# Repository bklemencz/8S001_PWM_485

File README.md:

# 8S001_PWM_485
2 or 3 Channel PWM Generator with RS485

Based on cheap 8PIN STM8S001 controller
Selectable 433Mhz EV1527/PT2262 Compatible Receiver Mode
Selectable PIR/Doppler Motion Sensor Inputs

Two versions:
One with low currect outputs, can be used as 3 channel with only RS485 active.
Other 2ch with 5A/30V NMOSFET outputs.

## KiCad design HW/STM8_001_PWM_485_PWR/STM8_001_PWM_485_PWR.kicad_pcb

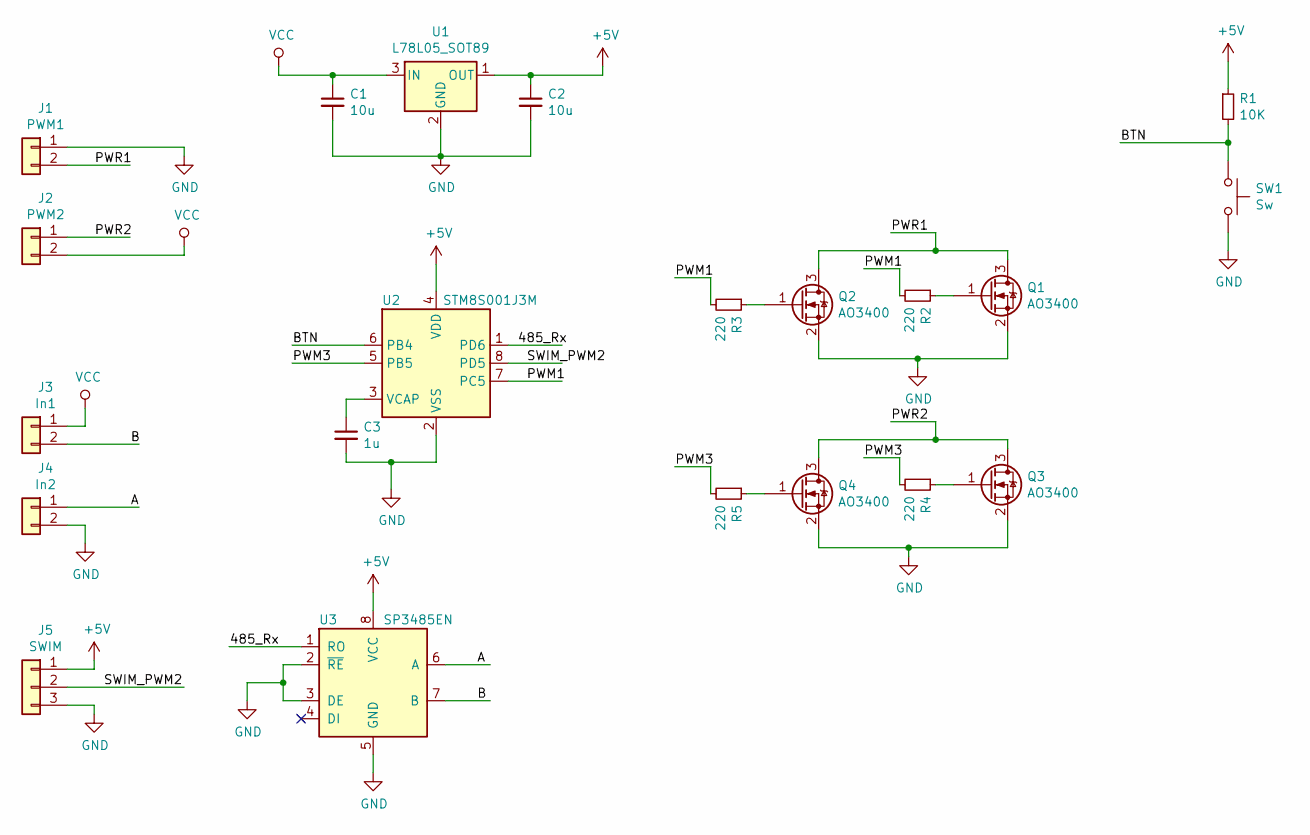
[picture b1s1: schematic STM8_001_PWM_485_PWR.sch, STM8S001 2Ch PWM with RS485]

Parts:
C1, C2: 10u; C_1206_3216Metric
C3: 1u; C_0805_2012Metric
J1: PWM1; TerminalBlock_Phoenix_PT-1,5-2-3.5-H_1x02_P3.50mm_Horizontal
J2: PWM2; TerminalBlock_Phoenix_PT-1,5-2-3.5-H_1x02_P3.50mm_Horizontal
J3: In1; TerminalBlock_Phoenix_PT-1,5-2-3.5-H_1x02_P3.50mm_Horizontal
J4: In2; TerminalBlock_Phoenix_PT-1,5-2-3.5-H_1x02_P3.50mm_Horizontal
J5: SWIM; PinHeader_1x03_P2.54mm_Vertical
Q1, Q2, Q3, Q4: AO3400; SOT-23
R1: 10K; R_0805_2012Metric
R2, R3, R4, R5: 220; R_0805_2012Metric
SW1: Sw; SW_SPST_CK_RS282G05A3
U1: L78L05_SOT89; SOT-89-3_Handsoldering
U2: STM8S001J3M; SOIC-8_3.9x4.9mm_P1.27mm
U3: SP3485EN; SOIC-8_3.9x4.9mm_P1.27mm

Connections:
+5V: C2.1, J5.1, R1.1, U1.1 (OUT), U2.4 (VDD), U3.8 (VCC)
/485_Rx: U2.1 (PD6), U3.1 (RO)
/A: J4.1, U3.6 (A)
/B: J3.2, U3.7 (B)
/BTN: R1.2, SW1.1, U2.6 (PB4)
/PWM1: R2.2, R3.2, U2.7 (PC5)
/PWM3: R4.2, R5.2, U2.5 (PB5)
/PWR1: J1.2, Q1.3 (D), Q2.3 (D)
/PWR2: J2.1, Q3.3 (D), Q4.3 (D)
/SWIM_PWM2: J5.2, U2.8 (PD5)
GND: C1.2, C2.2, C3.2, J1.1, J4.2, J5.3, Q1.2 (S), Q2.2 (S), Q3.2 (S), Q4.2 (S), SW1.2, U1.2 (GND), U2.2 (VSS), U3.2 (~RE~), U3.3 (DE), U3.5 (GND)
unnamed: C3.1, U2.3 (VCAP)
unnamed: Q1.1 (G), R2.1
unnamed: Q2.1 (G), R3.1
unnamed: Q3.1 (G), R4.1
unnamed: Q4.1 (G), R5.1
VCC: C1.1, J2.2, J3.1, U1.3 (IN)

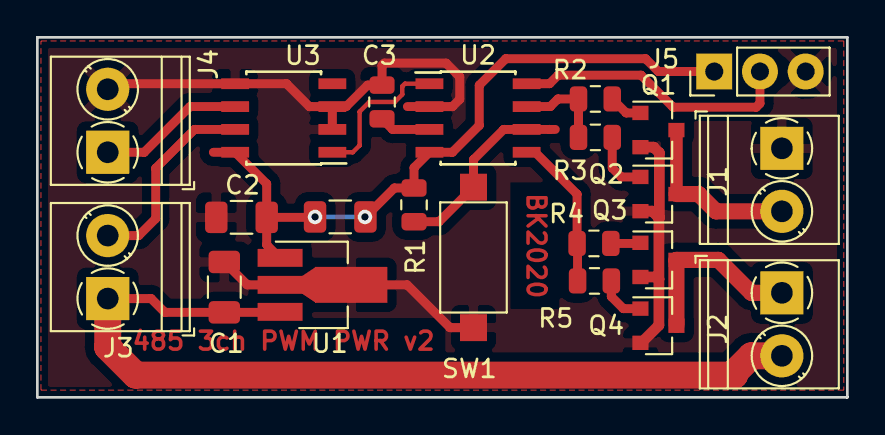
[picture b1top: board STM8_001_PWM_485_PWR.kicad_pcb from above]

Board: 2 copper layers, 45.0 x 20.0 mm, 21 parts (0 on the bottom side), 17 nets.

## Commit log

2020-12-01 Initial
2020-12-05 Serial OVR handling
2020-12-06 PCB Docs Cleanup
2020-12-10 v2.1 Shorter EV1527 Timeout
2021-01-28 DOC Update
